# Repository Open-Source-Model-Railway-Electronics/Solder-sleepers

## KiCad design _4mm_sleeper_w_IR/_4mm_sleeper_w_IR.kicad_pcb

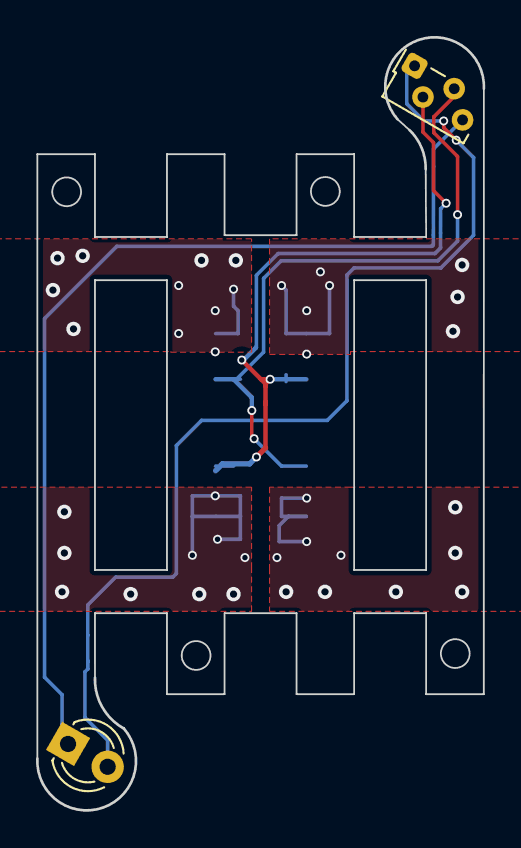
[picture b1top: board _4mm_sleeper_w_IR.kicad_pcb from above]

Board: 2 copper layers, 24.8 x 42.9 mm, 3 parts (1 on the bottom side), 4 nets.

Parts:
D101: LED; LED_D3.0mm
J106: Conn_02x05_Odd_Even; PinSocket_2x05_P2.54mm_Vertical_SMD
U101: IS471F; Sharp_IS471F

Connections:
/OUT: J106.4, J106.7, U101.2 (OUT)
GND: J106.3, J106.8, U101.3 (GND)
unnamed: D101.1 (K), U101.4 (GLo)
VCC: D101.2 (A), J106.5, J106.6, U101.1 (Vs)

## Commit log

2025-06-13 added initial files
2025-06-14 made production files
2025-06-17 added or renamed PNG preview
2025-06-23 added picture to readme file
2025-06-23 renamed hardware to docs
2025-06-23 fixed missing filey
